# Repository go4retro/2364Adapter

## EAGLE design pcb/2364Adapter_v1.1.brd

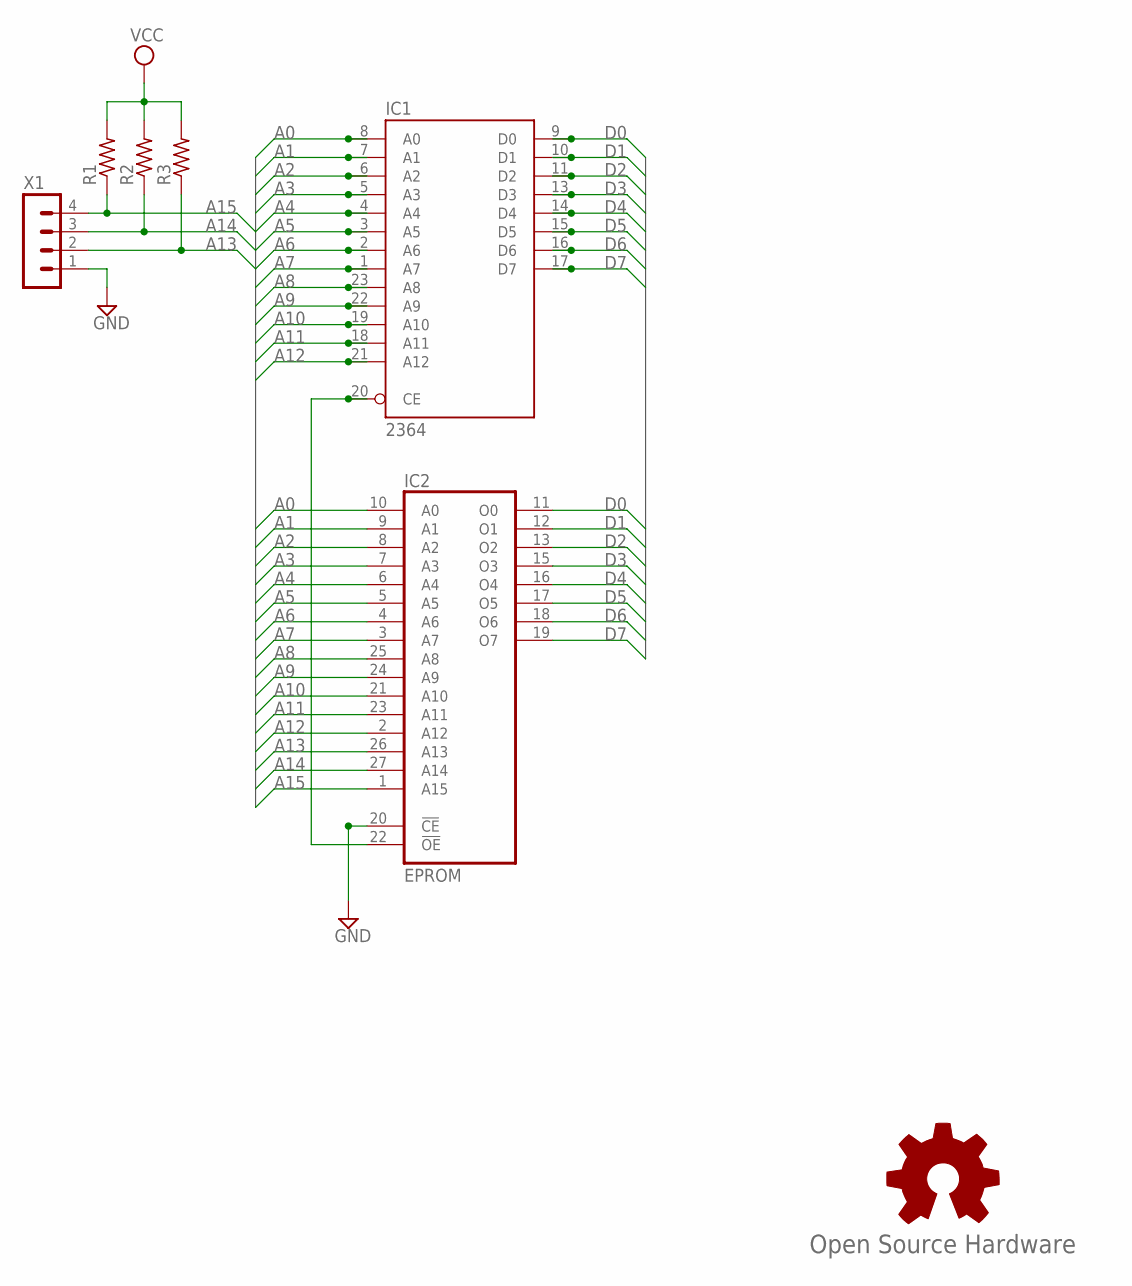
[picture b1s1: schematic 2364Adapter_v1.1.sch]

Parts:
GOLD_ORB_SM1: Open Source Hardware; OSHW_5MM
IC1: 2364; DIL24-ROUNDPAD
IC2: EPROM; DIL28-ROUNDPAD
R1, R2, R3: R-US_0204/5; 0204/5
X1: MA04-1

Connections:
A0: IC1.8 (A0), IC2.10 (A0)
A1: IC1.7 (A1), IC2.9 (A1)
A2: IC1.6 (A2), IC2.8 (A2)
A3: IC1.5 (A3), IC2.7 (A3)
A4: IC1.4 (A4), IC2.6 (A4)
A5: IC1.3 (A5), IC2.5 (A5)
A6: IC1.2 (A6), IC2.4 (A6)
A7: IC1.1 (A7), IC2.3 (A7)
A8: IC1.23 (A8), IC2.25 (A8)
A9: IC1.22 (A9), IC2.24 (A9)
A10: IC1.19 (A10), IC2.21 (A10)
A11: IC1.18 (A11), IC2.23 (A11)
A12: IC1.21 (A12), IC2.2 (A12)
A13: IC2.26 (A13), R1.1, X1.4
A14: IC2.27 (A14), R2.1, X1.3
A15: IC2.1 (A15), R3.1, X1.2
D0: IC1.9 (D0), IC2.11 (O0)
D1: IC1.10 (D1), IC2.12 (O1)
D2: IC1.11 (D2), IC2.13 (O2)
D3: IC1.13 (D3), IC2.15 (O3)
D4: IC1.14 (D4), IC2.16 (O4)
D5: IC1.15 (D5), IC2.17 (O5)
D6: IC1.16 (D6), IC2.18 (O6)
D7: IC1.17 (D7), IC2.19 (O7)
GND: IC1.12 (GND), IC2.14 (GND), IC2.20 (!CE), X1.1
unnamed: IC1.20 (CE), IC2.22 (!OE)
VCC: IC1.24 (VCC), IC2.28 (VCC), R1.2, R2.2, R3.2

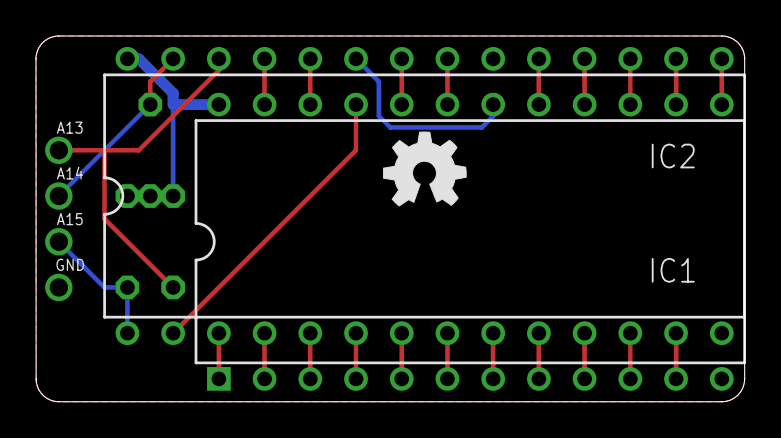
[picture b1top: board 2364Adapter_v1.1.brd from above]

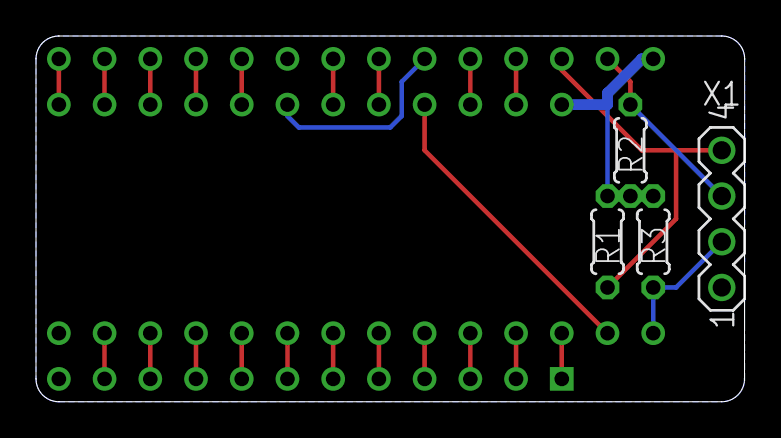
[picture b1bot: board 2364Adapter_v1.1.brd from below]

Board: 2 copper layers, 39.4 x 20.3 mm, 7 parts (4 on the bottom side), 27 nets.

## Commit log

2018-03-11 Updated license
2018-03-11 Added README.md
2018-05-30 Added PNG of Schematic
2025-08-09 Added media

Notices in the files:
pcb/2364Adapter_v1.1.brd:
(c) 2010 RETRO Innovations
